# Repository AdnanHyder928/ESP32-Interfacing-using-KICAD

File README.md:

<h1>Schematic Section</h1>

<h1>PCB Section</h1>

<h1>3D Model of PCB</h1>

Some 3D models are missing, but the footprints are there.

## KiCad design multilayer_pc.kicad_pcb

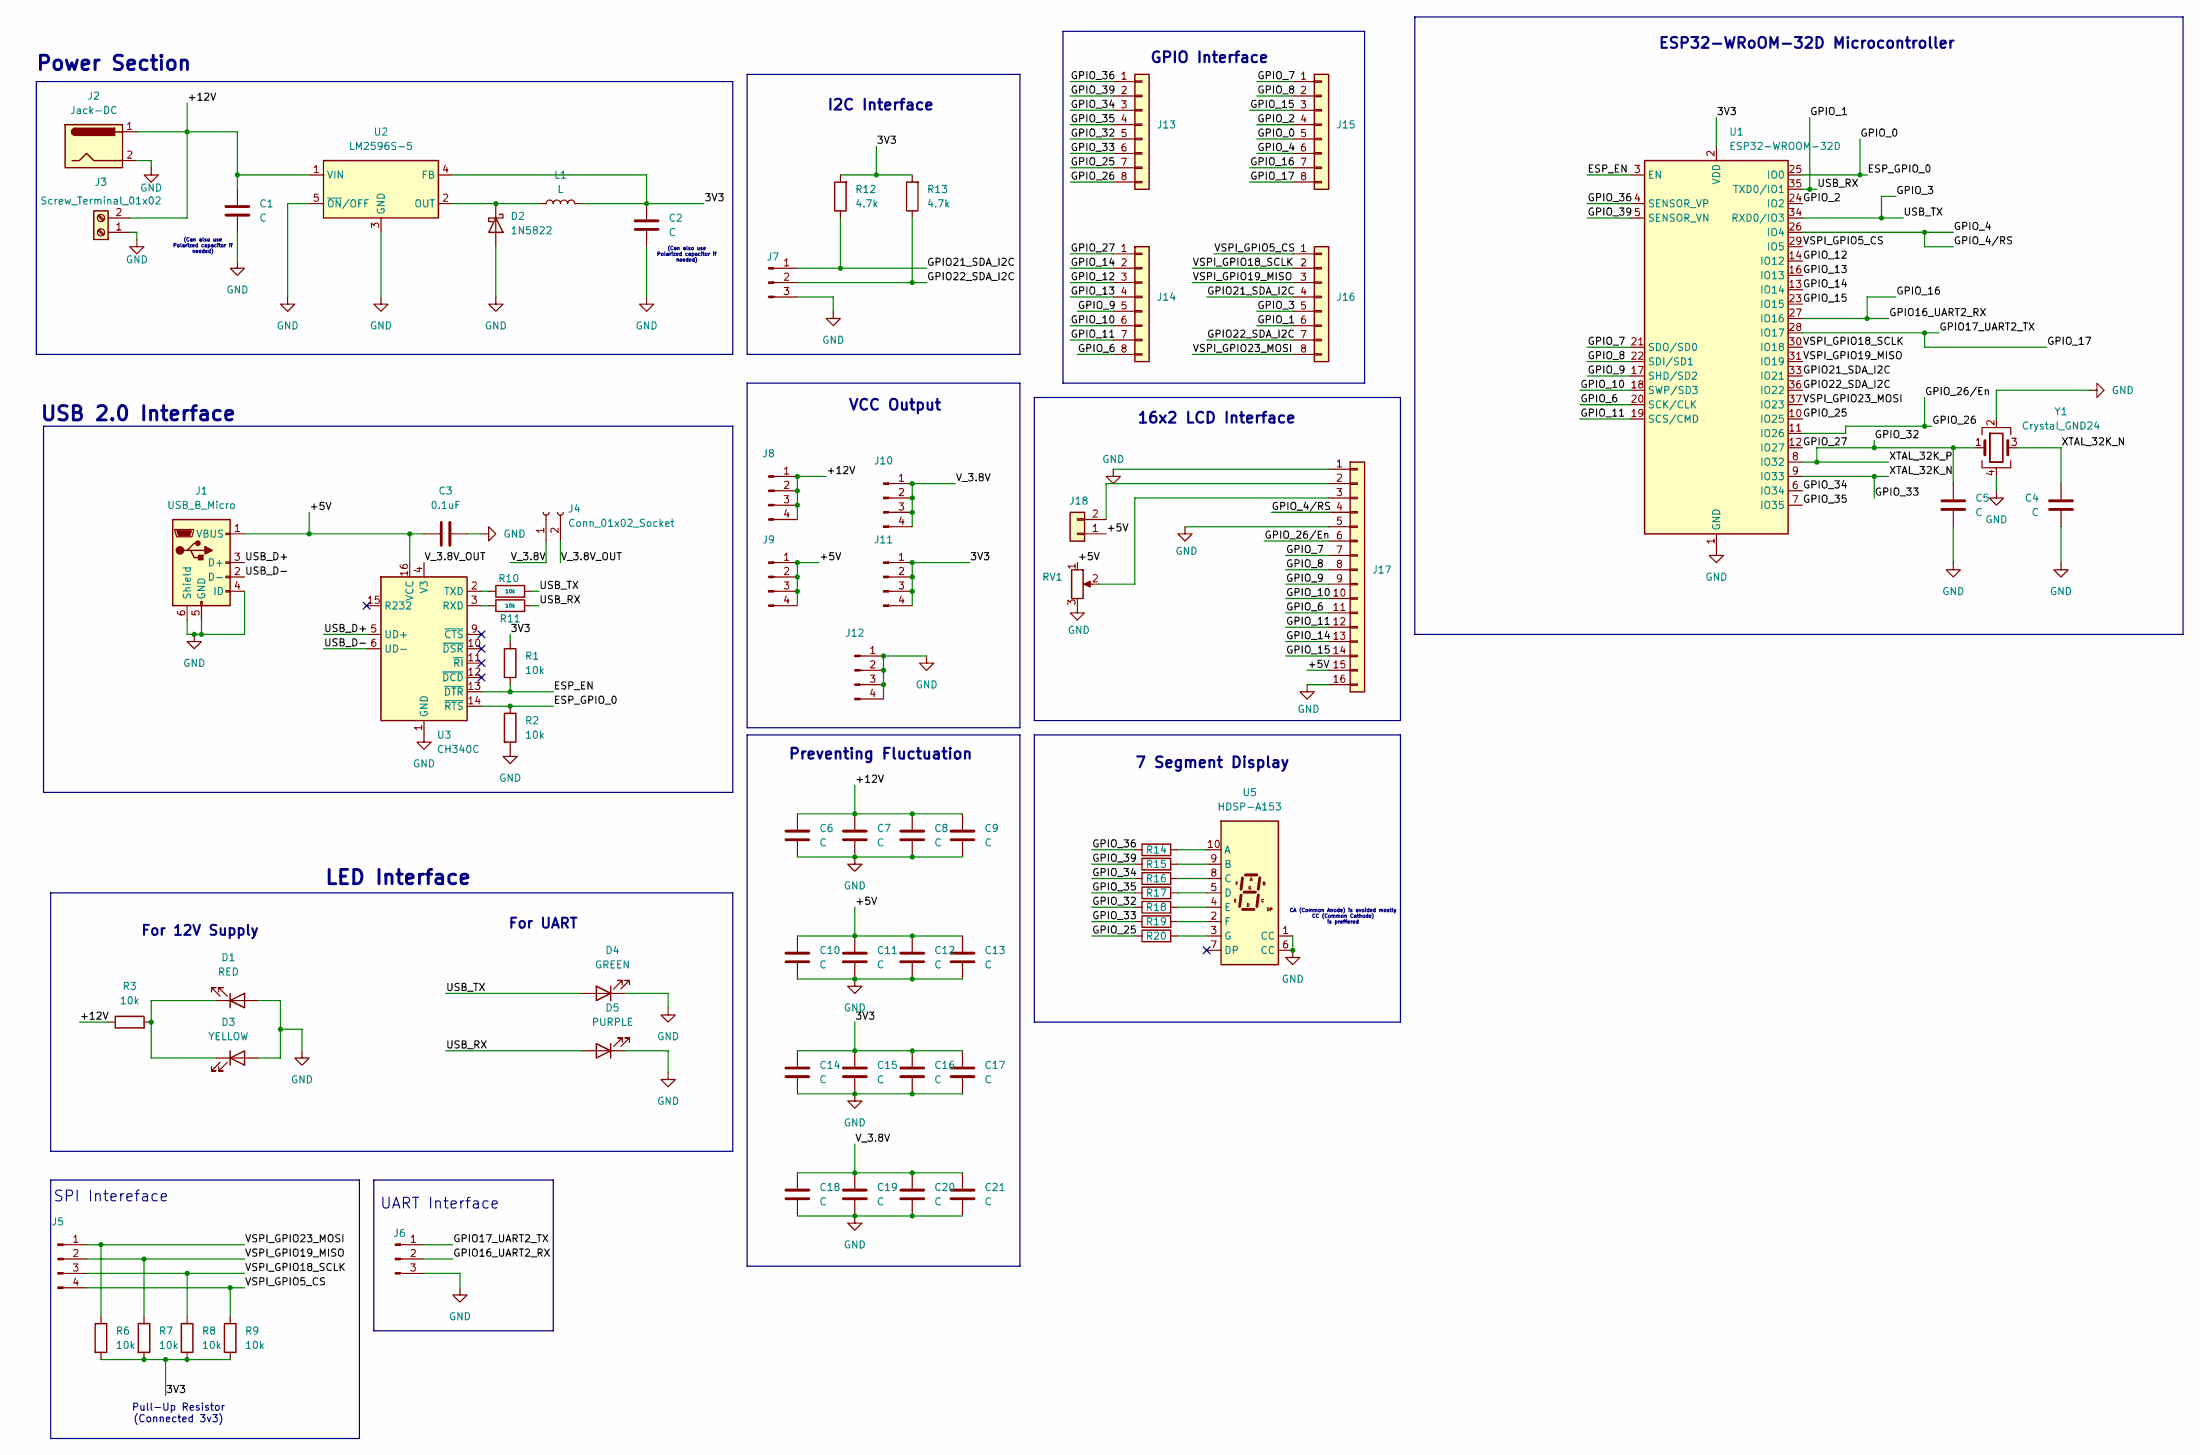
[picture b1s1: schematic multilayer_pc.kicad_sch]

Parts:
C1, C2, C4, C5, C6, C7, C8, C9, C10, C11, C12, C13, C14, C15, C16, C17, C18, C19, C20, C21: C; C_0805_2012Metric
C3: 0.1uF; C_0805_2012Metric
D1: RED; LED_0805_2012Metric
D2: 1N5822; D_DO-201AD_P15.24mm_Horizontal
D3: YELLOW; LED_0805_2012Metric
D4: GREEN; LED_0805_2012Metric
D5: PURPLE; LED_0805_2012Metric
J1: USB_B_Micro; USB_Micro-AB_Molex_47590-0001
J2: Jack-DC; BarrelJack_SwitchcraftConxall_RAPC10U_Horizontal
J3: Screw_Terminal_01x02; TerminalBlock_bornier-2_P5.08mm
J4: Conn_01x02_Socket; Molex_SL_171971-0002_1x02_P2.54mm_Vertical
J5, J8, J9, J10, J11, J12: Conn_01x04_Pin; FanPinHeader_1x04_P2.54mm_Vertical
J6, J7: Conn_01x03_Pin; FanPinHeader_1x03_P2.54mm_Vertical
J13, J14, J15, J16: Conn_01x08; Molex_KK-254_AE-6410-08A_1x08_P2.54mm_Vertical
J17: Conn_01x16; PinHeader_1x16_P2.54mm_Vertical
J18: Conn_01x02; PinHeader_1x02_P2.54mm_Vertical
L1: L; L_0805_2012Metric_Pad1.05x1.20mm_HandSolder
R1, R2, R3, R6, R7, R8, R9, R10, R11: 10k; R_0805_2012Metric
R12, R13: 4.7k; R_0805_2012Metric
R14, R15, R16, R17, R18, R19, R20: R_0805_2012Metric
RV1: R_Potentiometer; Potentiometer_Vishay_148-149_Single_Horizontal
U1: ESP32-WROOM-32D
U2: LM2596S-5; TO-263-5_TabPin3
U3: CH340C; SOIC-16_3.9x9.9mm_P1.27mm
U5: HDSP-A153; HDSP-A151
Y1: Crystal_GND24; Crystal_SMD_0603-2Pin_6.0x3.5mm

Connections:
/3V3: C2.1, C14.1, C15.1, C16.1, C17.1, J11.1, J11.2, J11.3, J11.4, L1.2, R1.1, R6.2, R7.2, R8.2, R9.2, R12.2, R13.2, U1.2 (VDD), U2.4 (FB)
/+5V: C3.1, C10.1, C11.1, C12.1, C13.1, J1.1 (VBUS), J9.1, J9.2, J9.3, J9.4, J17.15, J18.1, RV1.1, U3.16 (VCC)
/+12V: C1.1, C6.1, C7.1, C8.1, C9.1, J2.1, J3.2, J8.1, J8.2, J8.3, J8.4, R3.1, U2.1 (VIN)
/ESP_EN: R1.2, U1.3 (EN), U3.13 (~DTR)
/ESP_GPIO_0: J15.5, R2.1, U1.25 (IO0), U3.14 (~RTS)
/GPIO16_UART2_RX: J6.2, J15.7, U1.27 (IO16)
/GPIO17_UART2_TX: J6.1, J15.8, U1.28 (IO17)
/GPIO21_SDA_I2C: J7.1, J16.4, R12.1, U1.33 (IO21)
/GPIO22_SDA_I2C: J7.2, J16.7, R13.1, U1.36 (IO22)
/GPIO_1: D5.2 (A), J16.6, R11.2, U1.35 (TXD0/IO1); also elsewhere on the board
/GPIO_2: J15.4, U1.24 (IO2)
/GPIO_3: D4.2 (A), J16.5, R10.2, U1.34 (RXD0/IO3); also elsewhere on the board
/GPIO_4: J15.6, J17.4, U1.26 (IO4)
/GPIO_6: J14.8, J17.11, U1.20 (SCK/CLK)
/GPIO_7: J15.1, J17.7, U1.21 (SDO/SD0)
/GPIO_8: J15.2, J17.8, U1.22 (SDI/SD1)
/GPIO_9: J14.5, J17.9, U1.17 (SHD/SD2)
/GPIO_10: J14.6, J17.10, U1.18 (SWP/SD3)
/GPIO_11: J14.7, J17.12, U1.19 (SCS/CMD)
/GPIO_12: J14.3, U1.14 (IO12)
/GPIO_13: J14.4, U1.16 (IO13)
/GPIO_14: J14.2, J17.13, U1.13 (IO14)
/GPIO_15: J15.3, J17.14, U1.23 (IO15)
/GPIO_25: J13.7, R20.1, U1.10 (IO25)
/GPIO_26: J13.8, J17.6, U1.11 (IO26)
/GPIO_27: J14.1, U1.12 (IO27)
/GPIO_32: C5.1, J13.5, R18.1, U1.8 (IO32), Y1.1
/GPIO_33: C4.1, J13.6, R19.1, U1.9 (IO33), Y1.3
/GPIO_34: J13.3, R16.1, U1.6 (IO34)
/GPIO_35: J13.4, R17.1, U1.7 (IO35)
/GPIO_36: J13.1, R14.1, U1.4 (SENSOR_VP)
/GPIO_39: J13.2, R15.1, U1.5 (SENSOR_VN)
/USB_D+: J1.3 (D+), U3.5 (UD+)
/USB_D-: J1.2 (D-), U3.6 (UD-)
/VSPI_GPIO5_CS: J5.4, J16.1, R9.1, U1.29 (IO5)
/VSPI_GPIO18_SCLK: J5.3, J16.2, R8.1, U1.30 (IO18)
/VSPI_GPIO19_MISO: J5.2, J16.3, R7.1, U1.31 (IO19)
/VSPI_GPIO23_MOSI: J5.1, J16.8, R6.1, U1.37 (IO23)
/V_3.8V: C18.1, C19.1, C20.1, C21.1, J4.1, J10.1, J10.2, J10.3, J10.4
/V_3.8V_OUT: J4.2, U3.4 (V3)
GND: C1.2, C2.2, C3.2, C4.2, C5.2, C6.2, C7.2, C8.2, C9.2, C10.2, C11.2, C12.2, C13.2, C14.2, C15.2, C16.2, C17.2, C18.2, C19.2, C20.2, C21.2, D1.2 (A), D2.2 (A), D3.2 (A), D4.1 (K), D5.1 (K), J1.4 (ID), J1.5 (GND), J1.6 (Shield), J2.2, J3.1, J6.3, J7.3, J12.1, J12.2, J12.3, J12.4, J17.1, J17.5, J17.16, R2.2, RV1.3, U1.1 (GND), U1.15 (GND), U1.38 (GND), U1.39 (GND), U2.3 (GND), U2.5 (~ON/OFF), U3.1 (GND), U5.1 (CC), U5.6 (CC), Y1.2, Y1.4
unnamed: D1.1 (K), D3.1 (K), R3.2
unnamed: D2.1 (K), L1.1, U2.2 (OUT)
unnamed: J17.2, J18.2
unnamed: J17.3, RV1.2
unnamed: R11.1, U3.3 (RXD)
unnamed: R10.1, U3.2 (TXD)
unnamed: R14.2, U5.10 (A)
unnamed: R15.2, U5.9 (B)
unnamed: R16.2, U5.8 (C)
unnamed: R17.2, U5.5 (D)
unnamed: R18.2, U5.4 (E)
unnamed: R19.2, U5.2 (F)
unnamed: R20.2, U5.3 (G)

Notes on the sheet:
CA (Common Anode) is avoided mostly CC (Common Cathode) is preffered
GPIO Interface
VCC Output
For 12V Supply
For UART
(Can also use Polarized capacitor if needed)
I2C Interface
16x2 LCD Interface
SPI Intereface
7 Segment Display
Preventing Fluctuation
Pull-Up Resistor (Connected 3v3)
Power Section
USB 2.0 Interface
LED Interface
UART Interface
ESP32-WRoOM-32D Microcontroller

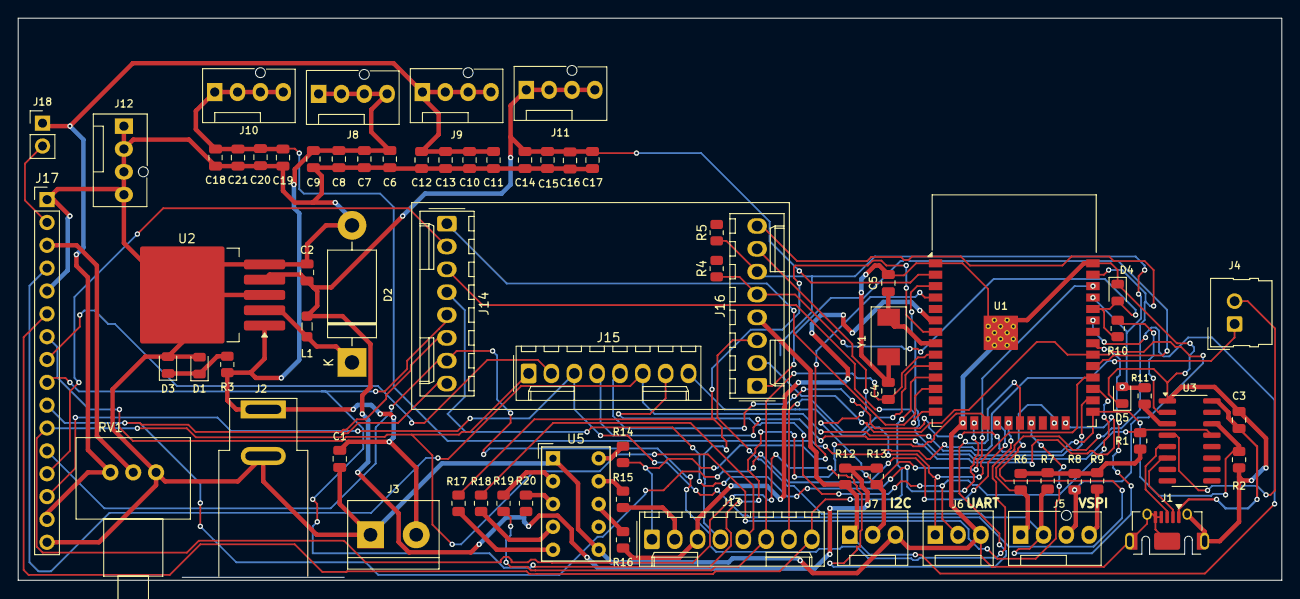
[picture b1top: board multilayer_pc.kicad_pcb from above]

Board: 2 copper layers, 140.4 x 62.4 mm, 71 parts (0 on the bottom side), 54 nets.

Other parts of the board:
R4, R5: 10k; R_0805_2012Metric

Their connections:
/GPIO_1: R5.1; also elsewhere on the board
/GPIO_3: R4.1; also elsewhere on the board

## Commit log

2025-04-14 Initial Commit with schematic only (Part 1)
2025-08-03 Updated The PCB of the Project
2025-12-29 Add schematic, PCB, and 3D model sections to README
    Added schematic, PCB, and 3D model sections with images.
